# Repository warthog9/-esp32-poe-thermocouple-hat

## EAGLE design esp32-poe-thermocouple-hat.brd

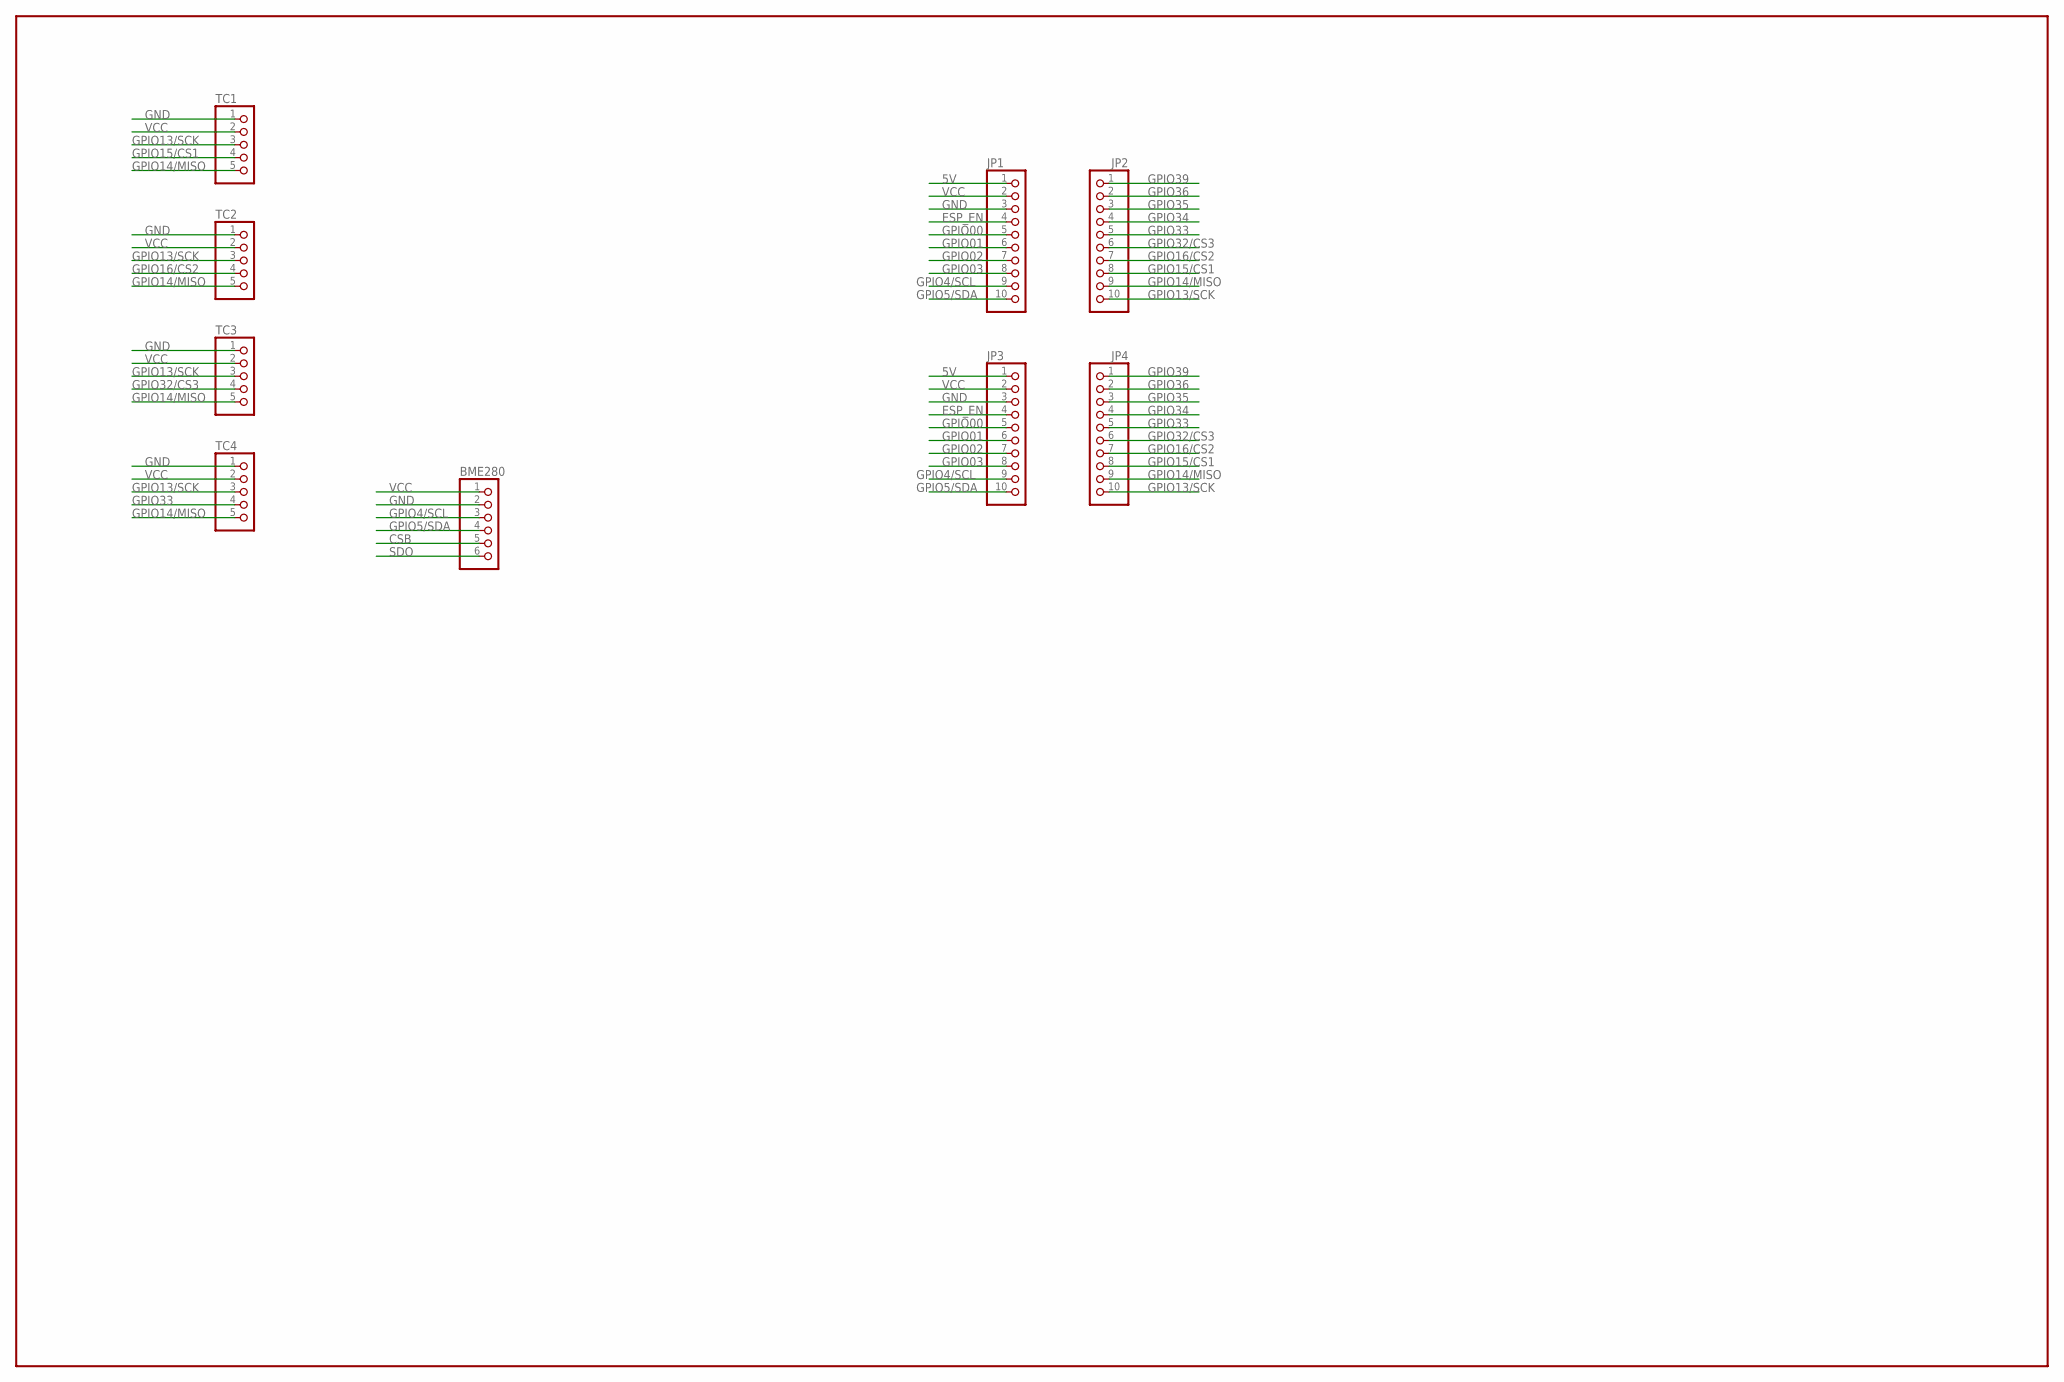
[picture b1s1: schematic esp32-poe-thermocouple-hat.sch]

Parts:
BME280: PINHD-1X6; 1X06
JP1, JP2, JP3, JP4: PINHD-1X10; 1X10
TC1, TC2, TC3, TC4: PINHD-1X5; 1X05

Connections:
5V: JP1.1, JP3.1
CSB: BME280.5
ESP_EN: JP1.4, JP3.4
GND: BME280.2, JP1.3, JP3.3, TC1.1, TC2.1, TC3.1, TC4.1
GPIO00: JP1.5, JP3.5
GPIO01: JP1.6, JP3.6
GPIO02: JP1.7, JP3.7
GPIO03: JP1.8, JP3.8
GPIO4/SCL: BME280.3, JP1.9, JP3.9
GPIO5/SDA: BME280.4, JP1.10, JP3.10
GPIO13/SCK: JP2.10, JP4.10, TC1.3, TC2.3, TC3.3, TC4.3
GPIO14/MISO: JP2.9, JP4.9, TC1.5, TC2.5, TC3.5, TC4.5
GPIO15/CS1: JP2.8, JP4.8, TC1.4
GPIO16/CS2: JP2.7, JP4.7, TC2.4
GPIO32/CS3: JP2.6, JP4.6, TC3.4
GPIO33: JP2.5, JP4.5, TC4.4
GPIO34: JP2.4, JP4.4
GPIO35: JP2.3, JP4.3
GPIO36: JP2.2, JP4.2
GPIO39: JP2.1, JP4.1
SDO: BME280.6
VCC: BME280.1, JP1.2, JP3.2, TC1.2, TC2.2, TC3.2, TC4.2

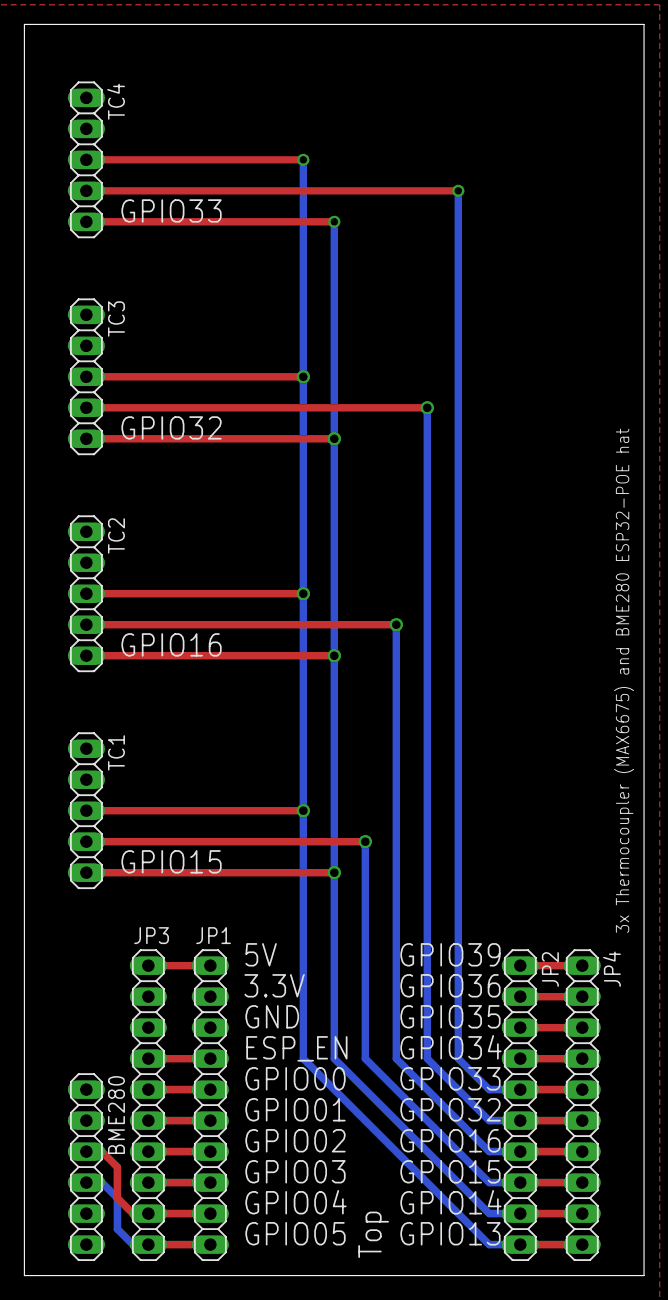
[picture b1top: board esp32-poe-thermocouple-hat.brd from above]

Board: 2 copper layers, 50.8 x 102.5 mm, 9 parts (0 on the bottom side), 20 nets.

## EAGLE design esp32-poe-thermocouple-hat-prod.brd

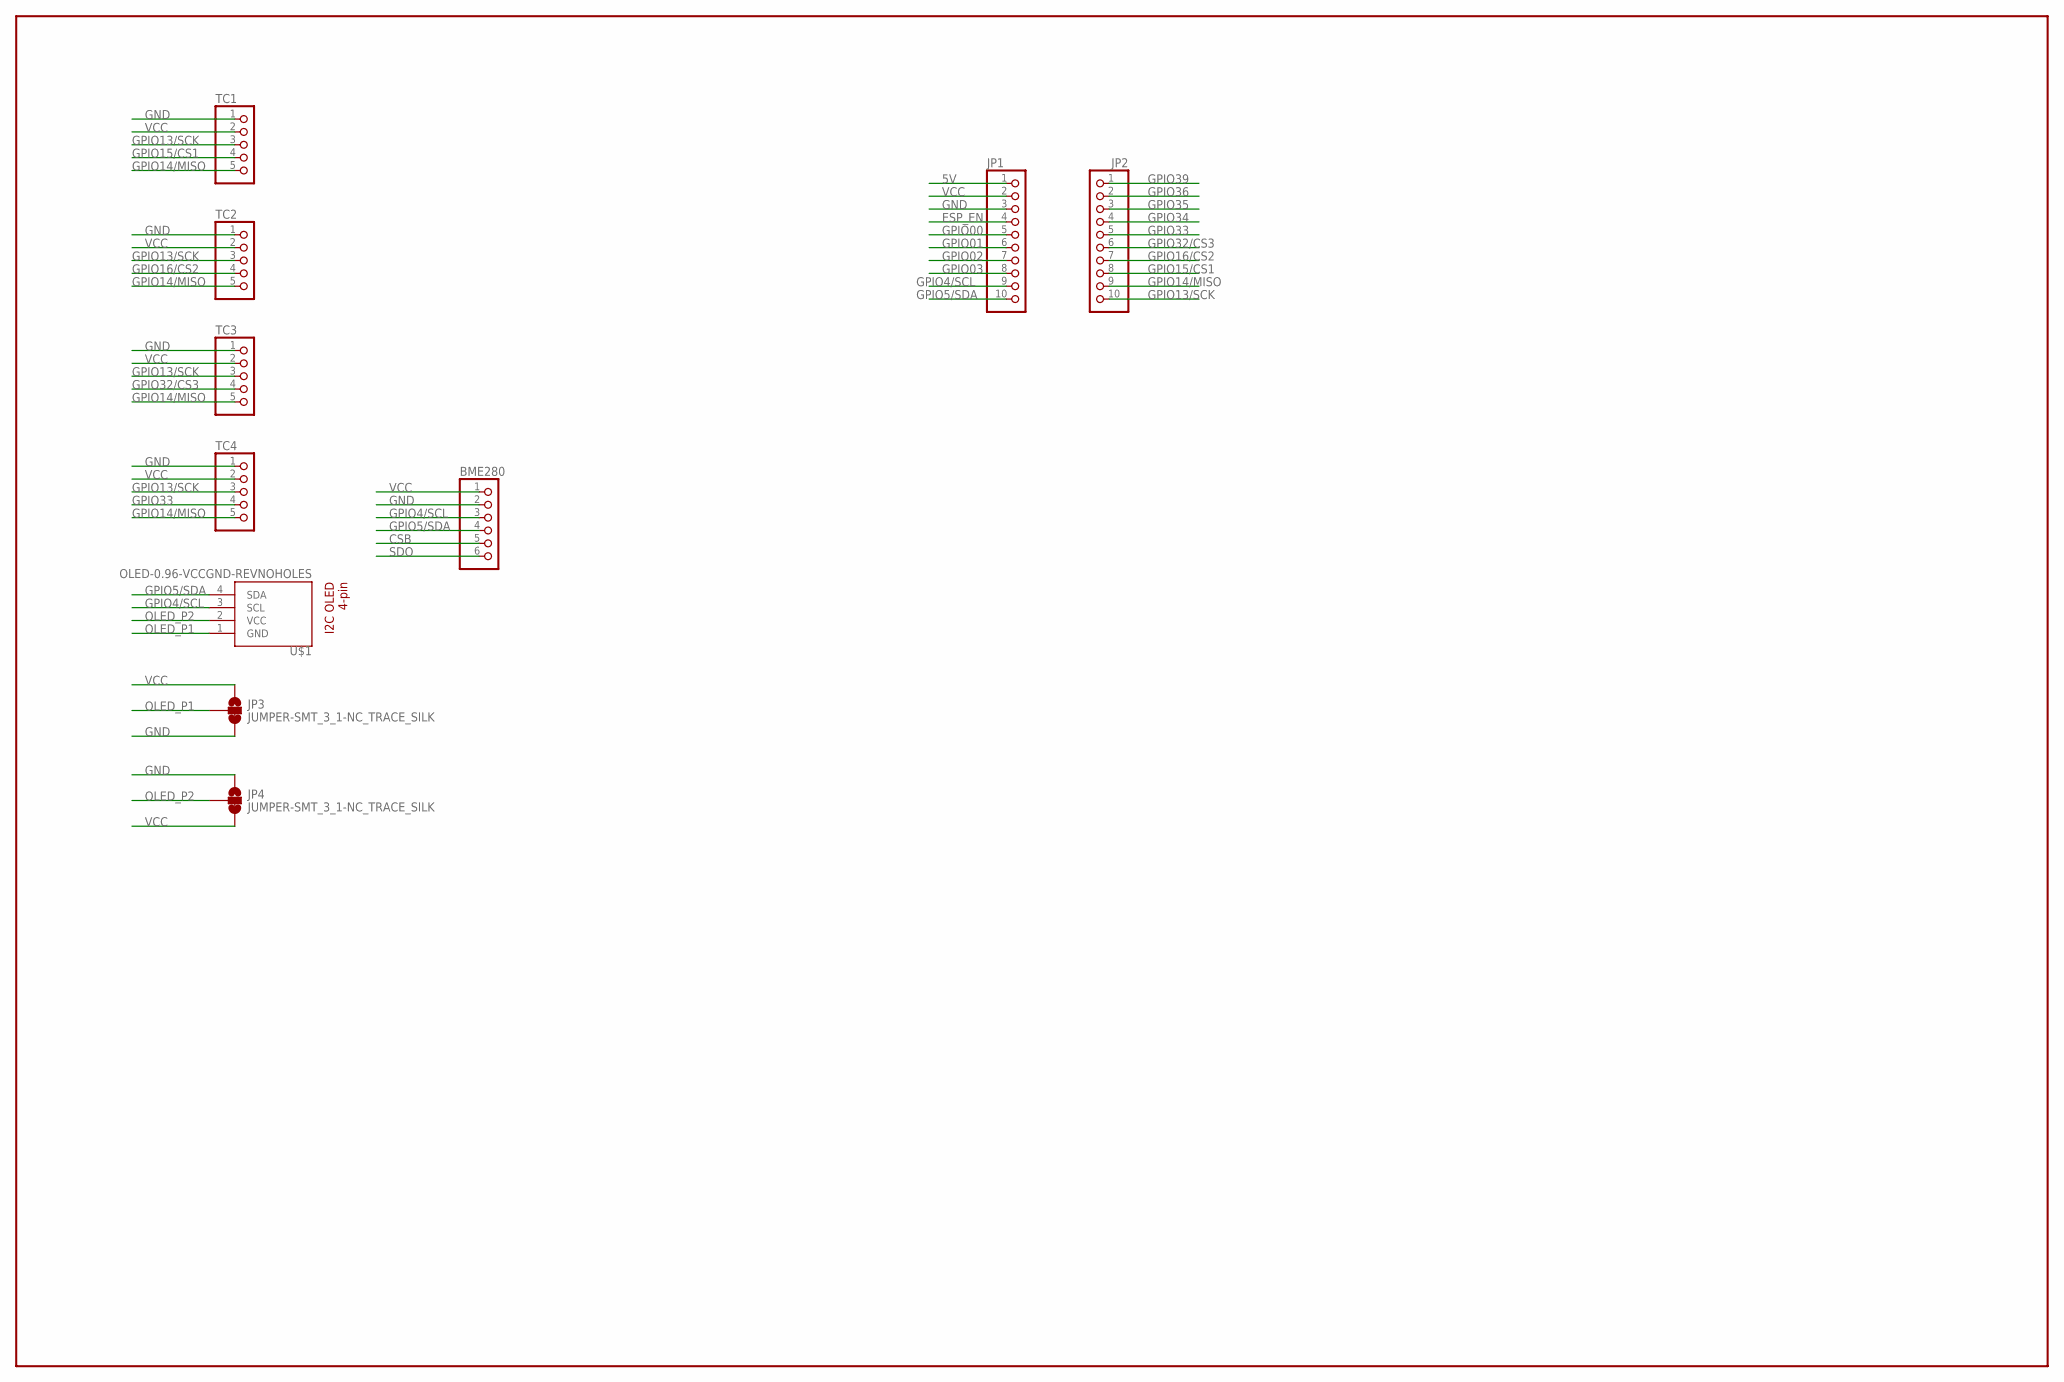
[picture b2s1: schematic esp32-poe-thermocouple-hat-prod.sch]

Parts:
BME280: PINHD-1X6; 1X06
JP1, JP2: PINHD-1X10; 1X10
JP3, JP4: JUMPER-SMT_3_1-NC_TRACE_SILK; SMT-JUMPER_3_1-NC_TRACE_SILK
TC1, TC2, TC3, TC4: PINHD-1X5; 1X05
U$1: OLED-0.96-VCCGND-REVNOHOLES; OLED-I2C-4PIN-NOHOLES

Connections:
5V: JP1.1
CSB: BME280.5
ESP_EN: JP1.4
GND: BME280.2, JP1.3, JP3.3, JP4.1, TC1.1, TC2.1, TC3.1, TC4.1
GPIO00: JP1.5
GPIO01: JP1.6
GPIO02: JP1.7
GPIO03: JP1.8
GPIO4/SCL: BME280.3, JP1.9, U$1.3 (SCL)
GPIO5/SDA: BME280.4, JP1.10, U$1.4 (SDA)
GPIO13/SCK: JP2.10, TC1.3, TC2.3, TC3.3, TC4.3
GPIO14/MISO: JP2.9, TC1.5, TC2.5, TC3.5, TC4.5
GPIO15/CS1: JP2.8, TC1.4
GPIO16/CS2: JP2.7, TC2.4
GPIO32/CS3: JP2.6, TC3.4
GPIO33: JP2.5, TC4.4
GPIO34: JP2.4
GPIO35: JP2.3
GPIO36: JP2.2
GPIO39: JP2.1
OLED_P1: JP3.2, U$1.1 (GND)
OLED_P2: JP4.2, U$1.2 (VCC)
SDO: BME280.6
VCC: BME280.1, JP1.2, JP3.1, JP4.3, TC1.2, TC2.2, TC3.2, TC4.2

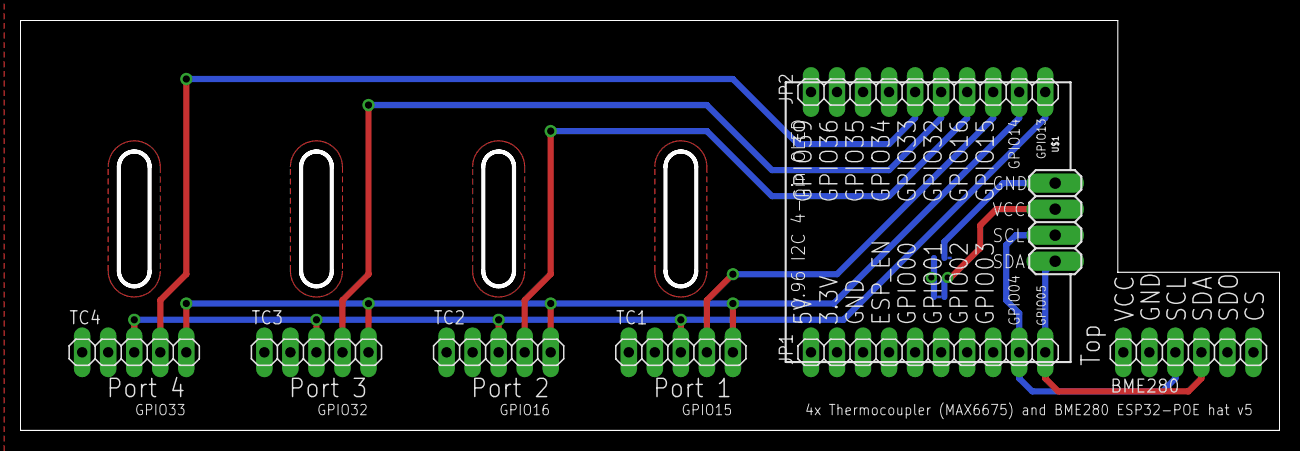
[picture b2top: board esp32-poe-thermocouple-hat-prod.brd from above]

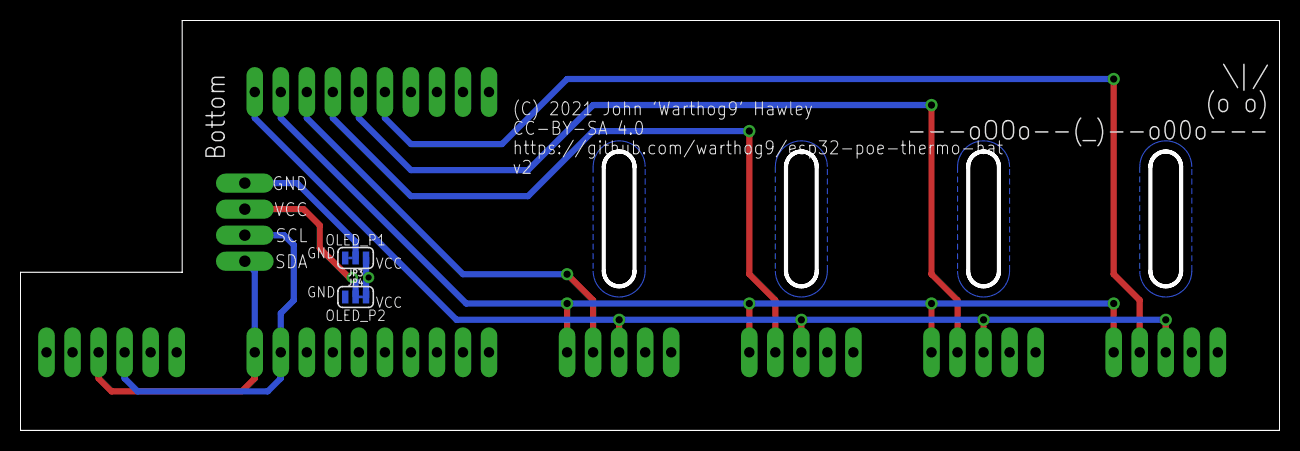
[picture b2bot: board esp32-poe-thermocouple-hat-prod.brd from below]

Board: 2 copper layers, 122.5 x 39.6 mm, 10 parts (2 on the bottom side), 12 nets.

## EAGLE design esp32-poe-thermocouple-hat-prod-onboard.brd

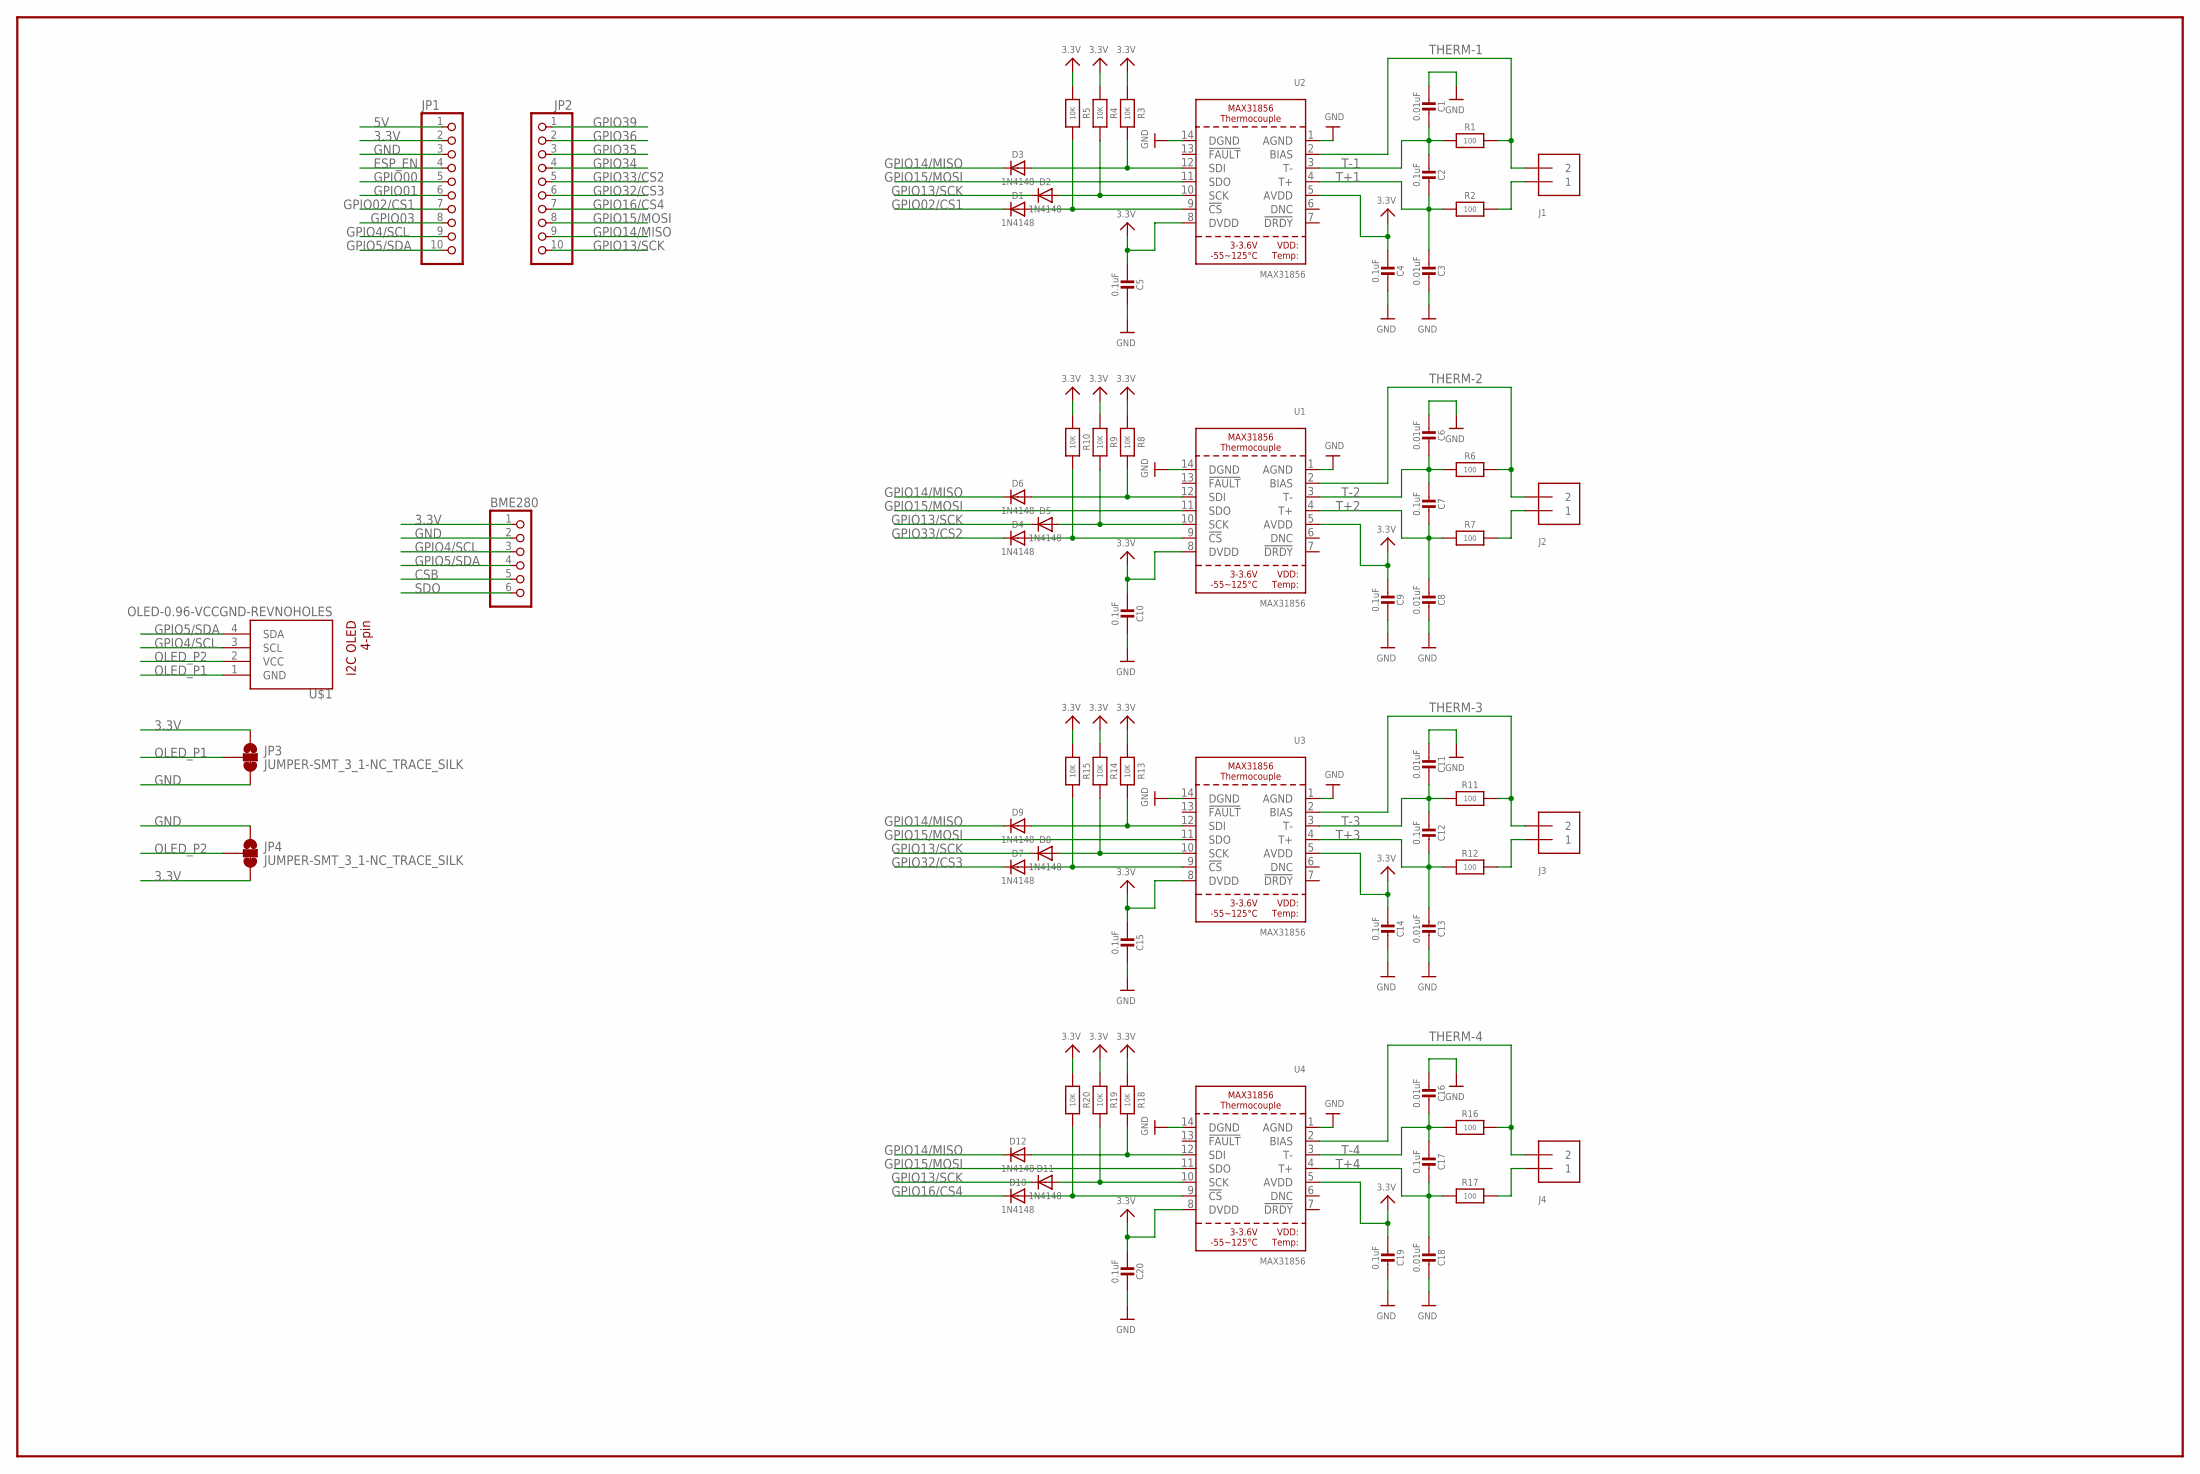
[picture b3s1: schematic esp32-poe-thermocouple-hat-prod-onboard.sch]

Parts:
BME280: PINHD-1X6; 1X06
C1, C6, C11, C16: 0.01uF; 0805_10MGAP
C2, C4, C5, C7, C9, C10, C12, C14, C15, C17, C19, C20: 0.1uF; 0805-NO
C3, C8, C13, C18: 0.01uF; 0805-NO
D1, D2, D3, D4, D5, D6, D7, D8, D9, D10, D11, D12: 1N4148; SOD-323
J1, J2, J3, J4: TERMBLOCK_1X2-7.62-SCREW; TERMBLOCK_1X2-7.62MM-SCREW
JP1, JP2: PINHD-1X10; 1X10
JP3, JP4: JUMPER-SMT_3_1-NC_TRACE_SILK; SMT-JUMPER_3_1-NC_TRACE_SILK
R1, R2, R6, R7, R11, R12, R16, R17: 100; 0805-NO
R3, R4, R5, R8, R9, R10, R13, R14, R15, R18, R19, R20: 10K; 0805-NO
U1, U2, U3, U4: MAX31856; TSSOP14
U$1: OLED-0.96-VCCGND-REVNOHOLES; OLED-I2C-4PIN-NOHOLES

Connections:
3.3V: BME280.1, C4.1, C5.1, C9.1, C10.1, C14.1, C15.1, C19.1, C20.1, JP1.2, JP3.1, JP4.3, R3.2, R4.2, R5.2, R8.2, R9.2, R10.2, R13.2, R14.2, R15.2, R18.2, R19.2, R20.2, U1.5 (AVDD), U1.8 (DVDD), U2.5 (AVDD), U2.8 (DVDD), U3.5 (AVDD), U3.8 (DVDD), U4.5 (AVDD), U4.8 (DVDD)
5V: JP1.1
!CS_3V: D1.A, R5.1, U2.9 (!CS)
!CS_3V1: D4.A, R10.1, U1.9 (!CS)
!CS_3V2: D7.A, R15.1, U3.9 (!CS)
!CS_3V3: D10.A, R20.1, U4.9 (!CS)
CSB: BME280.5
ESP_EN: JP1.4
GND: BME280.2, C1.1, C3.2, C4.2, C5.2, C6.1, C8.2, C9.2, C10.2, C11.1, C13.2, C14.2, C15.2, C16.1, C18.2, C19.2, C20.2, JP1.3, JP3.3, JP4.1, U1.1 (AGND), U1.14 (DGND), U2.1 (AGND), U2.14 (DGND), U3.1 (AGND), U3.14 (DGND), U4.1 (AGND), U4.14 (DGND)
GPIO00: JP1.5
GPIO01: JP1.6
GPIO02/CS1: D1.C, JP1.7
GPIO03: JP1.8
GPIO4/SCL: BME280.3, JP1.9, U$1.3 (SCL)
GPIO5/SDA: BME280.4, JP1.10, U$1.4 (SDA)
GPIO13/SCK: D2.C, D5.C, D8.C, D11.C, JP2.10
GPIO14/MISO: D3.C, D6.C, D9.C, D12.C, JP2.9
GPIO15/MOSI: JP2.8, U1.11 (SDO), U2.11 (SDO), U3.11 (SDO), U4.11 (SDO)
GPIO16/CS4: D10.C, JP2.7
GPIO32/CS3: D7.C, JP2.6
GPIO33/CS2: D4.C, JP2.5
GPIO34: JP2.4
GPIO35: JP2.3
GPIO36: JP2.2
GPIO39: JP2.1
OLED_P1: JP3.2, U$1.1 (GND)
OLED_P2: JP4.2, U$1.2 (VCC)
SCK_3V: D2.A, R4.1, U2.10 (SCK)
SCK_3V1: D5.A, R9.1, U1.10 (SCK)
SCK_3V2: D8.A, R14.1, U3.10 (SCK)
SCK_3V3: D11.A, R19.1, U4.10 (SCK)
SDO: BME280.6
SDO_3V: D3.A, R3.1, U2.12 (SDI)
SDO_3V1: D6.A, R8.1, U1.12 (SDI)
SDO_3V2: D9.A, R13.1, U3.12 (SDI)
SDO_3V3: D12.A, R18.1, U4.12 (SDI)
T+1: C2.2, C3.1, R2.2, U2.4 (T+)
T+2: C7.2, C8.1, R7.2, U1.4 (T+)
T+3: C12.2, C13.1, R12.2, U3.4 (T+)
T+4: C17.2, C18.1, R17.2, U4.4 (T+)
T-1: C1.2, C2.1, R1.2, U2.3 (T-)
T-2: C6.2, C7.1, R6.2, U1.3 (T-)
T-3: C11.2, C12.1, R11.2, U3.3 (T-)
T-4: C16.2, C17.1, R16.2, U4.3 (T-)
THERM+1: J1.1, R2.1
THERM+2: J2.1, R7.1
THERM+3: J3.1, R12.1
THERM+4: J4.1, R17.1
THERM-1: J1.2, R1.1, U2.2 (BIAS)
THERM-2: J2.2, R6.1, U1.2 (BIAS)
THERM-3: J3.2, R11.1, U3.2 (BIAS)
THERM-4: J4.2, R16.1, U4.2 (BIAS)

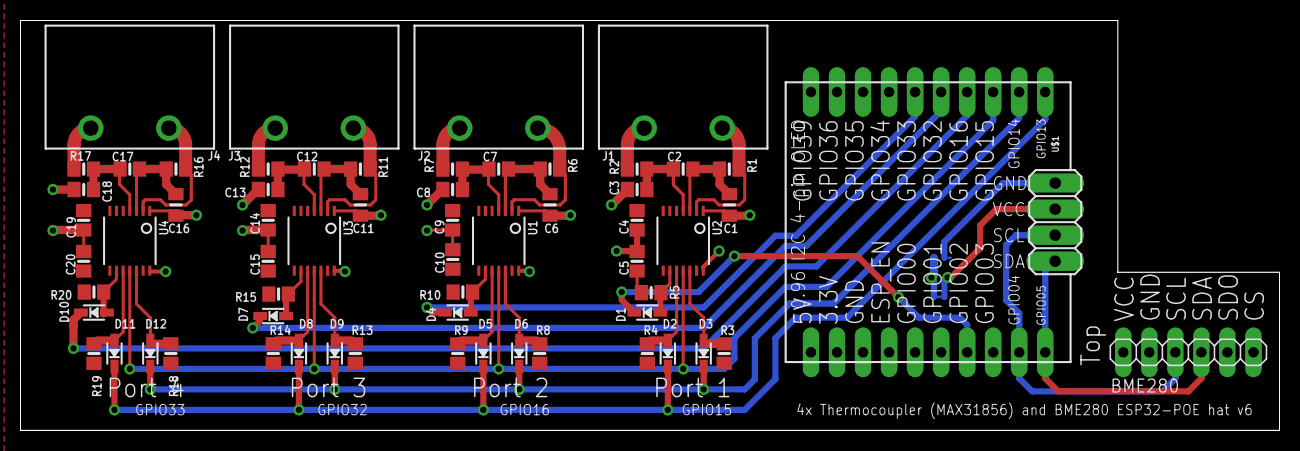
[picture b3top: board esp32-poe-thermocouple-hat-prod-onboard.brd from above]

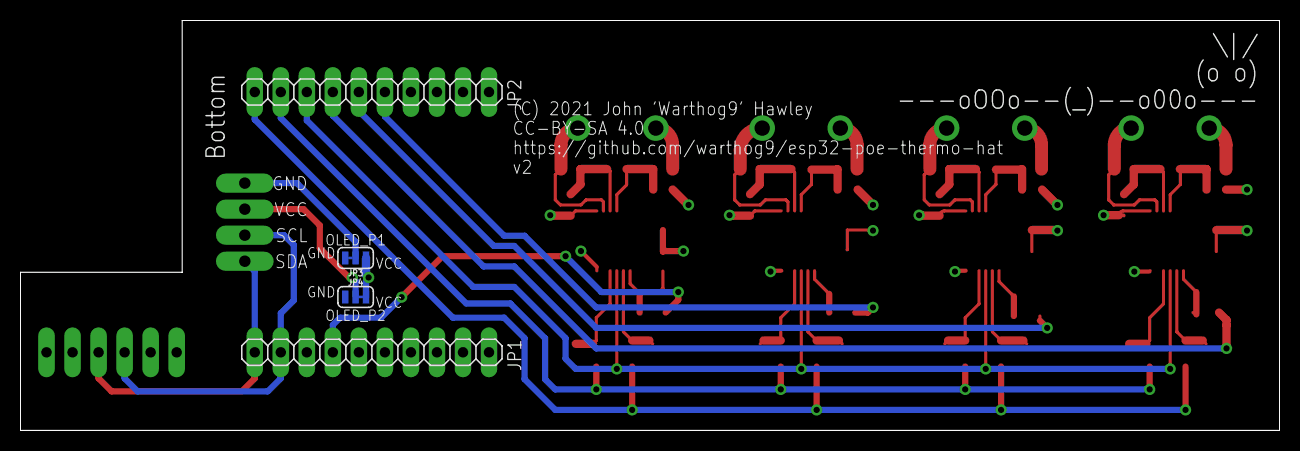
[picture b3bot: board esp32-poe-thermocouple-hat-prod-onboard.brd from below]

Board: 2 copper layers, 122.9 x 40.0 mm, 66 parts (4 on the bottom side), 41 nets.

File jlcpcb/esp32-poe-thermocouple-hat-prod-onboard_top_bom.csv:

Comment,Designator,Footprint,LCSC Part #
0.1uF,C2 C4 C5 C7 C9 C10 C12 C14 C15 C17 C19 C20,0805-NO,C38141 
0.01uF,C1,0805_10MGAP,C83170 
0.01uF,C3,0805-NO,C83170 
0.01uF,C6,0805_10MGAP,C83170 
0.01uF,C8,0805-NO,C83170 
0.01uF,C11,0805_10MGAP,C83170 
0.01uF,C13,0805-NO,C83170 
0.01uF,C16,0805_10MGAP,C83170 
0.01uF,C18,0805-NO,C83170 
1N4148,D1 D2 D3 D4 D5 D6 D7 D8 D9 D10 D11 D12,SOD-323,C2128 
10K,R3 R4 R5 R8 R9 R10 R13 R14 R15 R18 R19 R20,0805-NO,C17414 
100,R1 R2 R6 R7 R11 R12 R16 R17,0805-NO,C17408 
MAX31856,U1 U2 U3 U4,TSSOP14,C2653162

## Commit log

2023-12-08 Initial commit
    Ok this is the worst initial commit I could possibly do, mostly because
    this project has literally been going for years. This is the
    culmination of a few years worth of poking around and building things.
    It's progressed from standalone sensors attached to a board to being on
    the board, different chips, etc.
    I'm using the max31856 design (prod-onboard) right now. Channel 4 is

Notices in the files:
esp32-poe-thermocouple-hat-prod-onboard.brd:
(C) 2021 John 'Warthog9' Hawley
CC-BY-SA 4.0
parts and their libraries:
SparkFun-Jumpers: Licensing: Creative Commons ShareAlike 4.0 International - https://creativecommons.org/licenses/by-sa/4.0
microbuilder: This work is placed in the public domain, and may be freely used for commercial and non-commercial work with the following conditions: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
